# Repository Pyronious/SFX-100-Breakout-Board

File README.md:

# SFX-100-Breakout-Board
An Arduino Leonardo shield to simplify the wiring of SFX-100 serial port connectors

For more information about the SFX-100 project, please visit:
https://opensfx.com/

The "Group Buy Edition" is the latest and greatest.

The prototype works fine and uses the RJ45 connector for the E-stop instead of a screw terminal.

Releases
========
v1.35 April 24, 2019
A small modification to allow support for external power supplies higher than +5v. Not really necessary for our use case as powering by USB works fine and is typical for this application. But just in case someone out there does it differently for some reason. :)

========
v1.34 April 6, 2019
Group buy edition

This is the version of the board that was manufactured for the Group Buy.

* Replaced the modular jack with a screw terminal connector for simplicity and cost reduction.

* Removed JP1. You can shunt the screw terminal to test.

* DB25 connectors are now more symmetrical on the board for a cleaner design

* Board traces simplified and vias eliminated.

* Trace thickness increased

* Added additional holes for M3 mounting

* Updated enclosure

========
v1.32 March 23, 2019
Intial public release

J1 is a modular connector for running an Ethernet cable to your e-stop. You need to connect the wires from pins 1 and 8 to your e-stop switch.

If you are not using an e-stop, you must install a shunt jumper across JP1 to enable the circuit.

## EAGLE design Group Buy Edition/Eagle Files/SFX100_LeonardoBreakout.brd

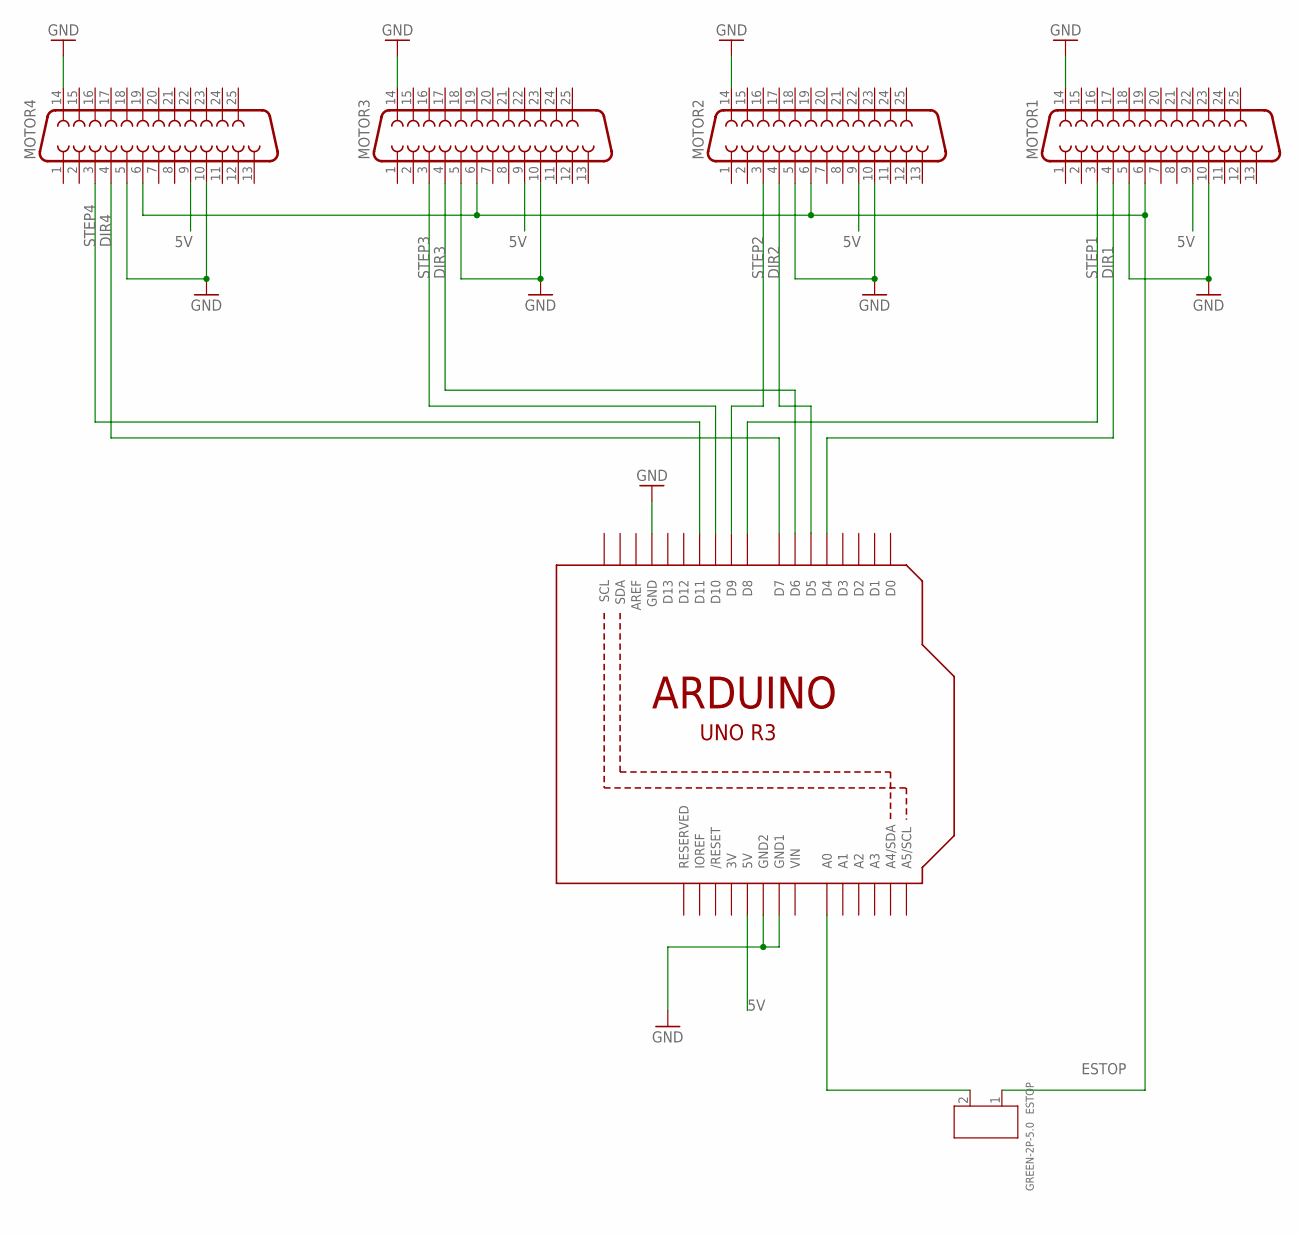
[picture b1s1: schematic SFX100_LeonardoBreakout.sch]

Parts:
ESTOP: GREEN-2P-5.0; H2-5.0-10.5X8.0MM
MOTOR1, MOTOR2, MOTOR3, MOTOR4: F25V
U1: ARDUINOR3-BPLACE

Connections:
3V: U1.3V
5V: MOTOR1.9, MOTOR2.9, MOTOR3.9, MOTOR4.9, U1.5V
DIR1: MOTOR1.4, U1.D4
DIR2: MOTOR2.4, U1.D5
DIR3: MOTOR3.4, U1.D6
DIR4: MOTOR4.4, U1.D7
ENA: ESTOP.2, U1.A0
ESTOP: ESTOP.1, MOTOR1.6, MOTOR2.6, MOTOR3.6, MOTOR4.6
GND: MOTOR1.5, MOTOR1.10, MOTOR1.14, MOTOR2.5, MOTOR2.10, MOTOR2.14, MOTOR3.5, MOTOR3.10, MOTOR3.14, MOTOR4.5, MOTOR4.10, MOTOR4.14, U1.GND, U1.GND1, U1.GND2
STEP1: MOTOR1.3, U1.D8
STEP2: MOTOR2.3, U1.D9
STEP3: MOTOR3.3, U1.D10
STEP4: MOTOR4.3, U1.D11
VIN: U1.VIN

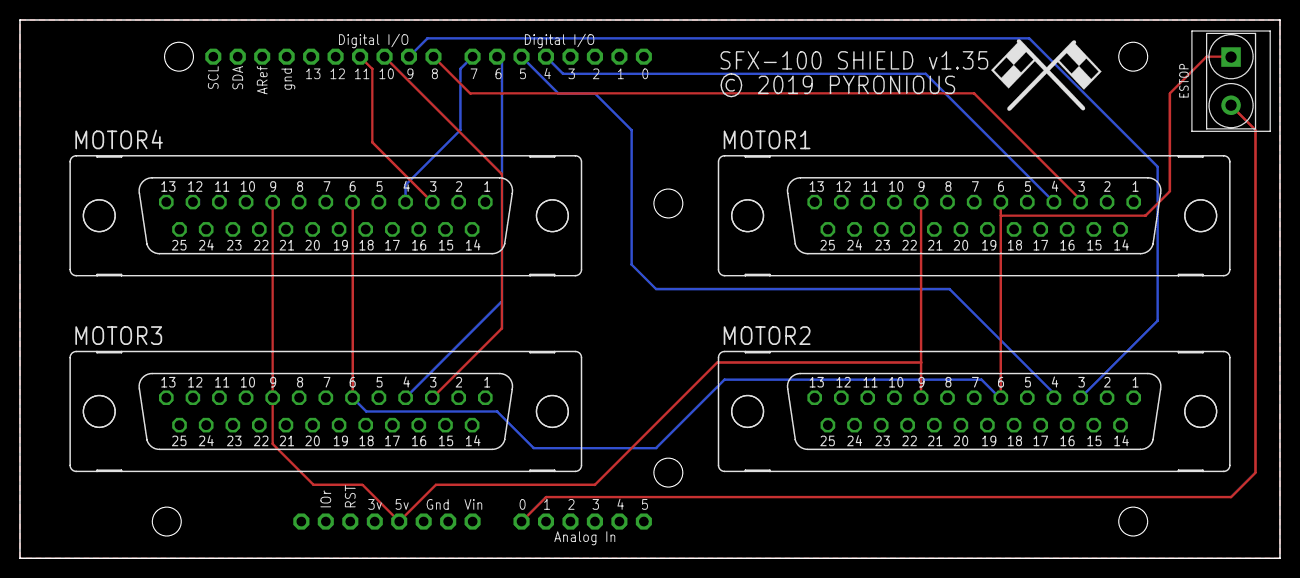
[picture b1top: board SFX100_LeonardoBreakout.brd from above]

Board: 2 copper layers, 130.8 x 55.9 mm, 6 parts (0 on the bottom side), 12 nets.

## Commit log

2019-03-24 Initial Release
    Added initial public release of Gerber files, Eagle files, and bill of materials.
2019-03-24 Update LICENSE
    Updated license to align with the SFX-100 project license.
2019-03-27 Added 3D printable enclosure
    STL files now included for printing a box and lid.
2019-04-07 Updated to v1.34 "Group Buy" Edition
    v1.34 April 6, 2019
    Group buy edition
    This is the version of the board that was manufactured for the Group Buy.
    * Replaced the modular jack with a screw terminal connector for simplicity and cost reduction.
    * Removed JP1. You can shunt the screw terminal to test.
    * DB25 connectors are now more symmetrical on the board for a cleaner design
2019-04-20 Create SFX100_Shield_Box_M8_feet_v134.stl
    Added a new enclosure type with feet on the side for M8 socket cap screws.
2019-04-24 Updated to final "group buy" design.
2019-04-24 Housekeeping update
    Renamed folders to "Group Buy Edition" and "Prototype Edition". Updated readme.
2021-02-04 Create FUNDING.yml
    Added donation button. Thank you for your support!
2021-02-04 Revert "Update FUNDING.yml"
    This reverts commit a2fb37df5b342f02e9bebef53fa0016d0bdf45bb.

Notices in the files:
Group Buy Edition/Eagle Files/SFX100_LeonardoBreakout.brd:
© 2019 PYRONIOUS
